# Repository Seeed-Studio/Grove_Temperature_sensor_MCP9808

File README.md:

Grove Temperature sensor MCP9808  
==============

Introduction of sensor
----------------------------  
Microchip Technology Inc.’s MCP9808 digital temperature sensor converts temperatures between -20°C and +100°C to a digital word with
±0.25°C/±0.5°C (typical/maximum) accuracy.  

***
Usage:
==========
Download all the source files.
There are two examples for user to use.
>* **example/MCP9808_basic_demo/MCP9808_basic_demo.ino**:This example is a sample use of temperature sensor,you need to polling for data. 
>* **example/MCP9808_demo_with_limit/MCP9808_demo_with_limit.ino**,There is a alert pad on the sensor module which connect to alert pin.You can set temperature limits by calling the API we provided.The alert pin outputs low when the temperature value beyond limit.Otherwise stays high.You can attach alert pin to a interrupt pin of host,To improve the efficiency of program operation.

Reference:
===============
Refer to the **/doc** to get more detail.

***
This software is written by downey  for seeed studio<br>
Email:dao.huang@seeed.cc
and is licensed under [The MIT License](http://opensource.org/licenses/mit-license.php). Check License.txt for more information.<br>

Contributing to this software is warmly welcomed. You can do this basically by<br>
[forking](https://help.github.com/articles/fork-a-repo), committing modifications and then [pulling requests](https://help.github.com/articles/using-pull-requests) (follow the links above<br>
for operating guide). Adding change log and your contact into file header is encouraged.<br>
Thanks for your contribution.

Seeed Studio is an open hardware facilitation company based in Shenzhen, China. <br>
Benefiting from local manufacture power and convenient global logistic system, <br>
we integrate resources to serve new era of innovation. Seeed also works with <br>
global distributors and partners to push open hardware movement.<br>

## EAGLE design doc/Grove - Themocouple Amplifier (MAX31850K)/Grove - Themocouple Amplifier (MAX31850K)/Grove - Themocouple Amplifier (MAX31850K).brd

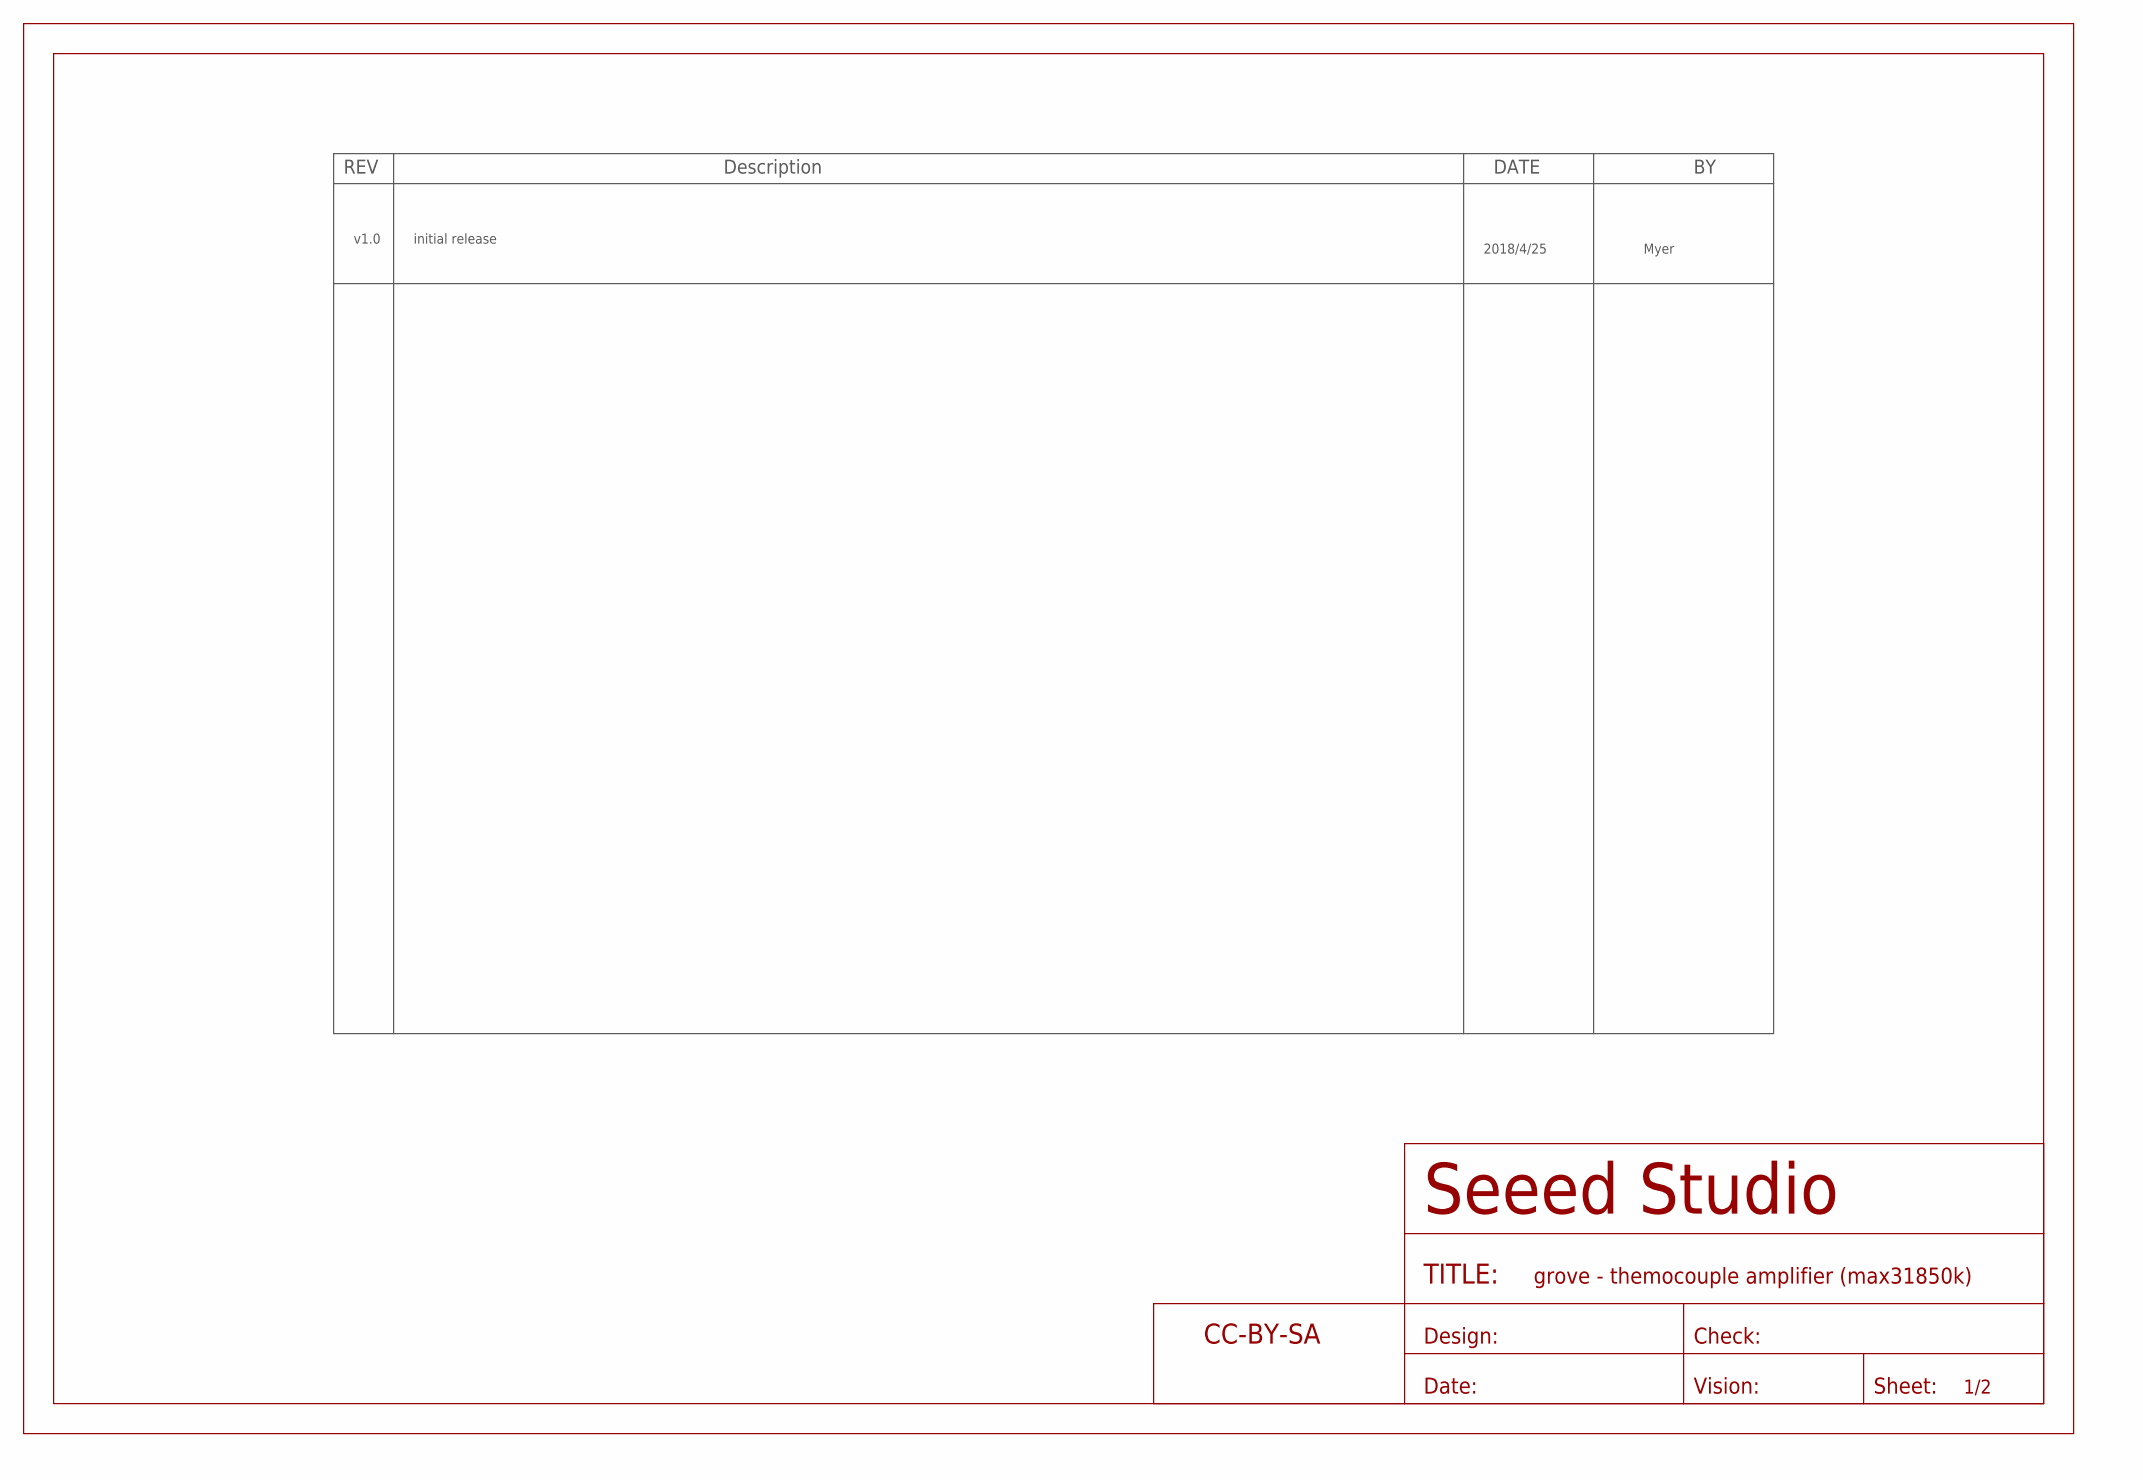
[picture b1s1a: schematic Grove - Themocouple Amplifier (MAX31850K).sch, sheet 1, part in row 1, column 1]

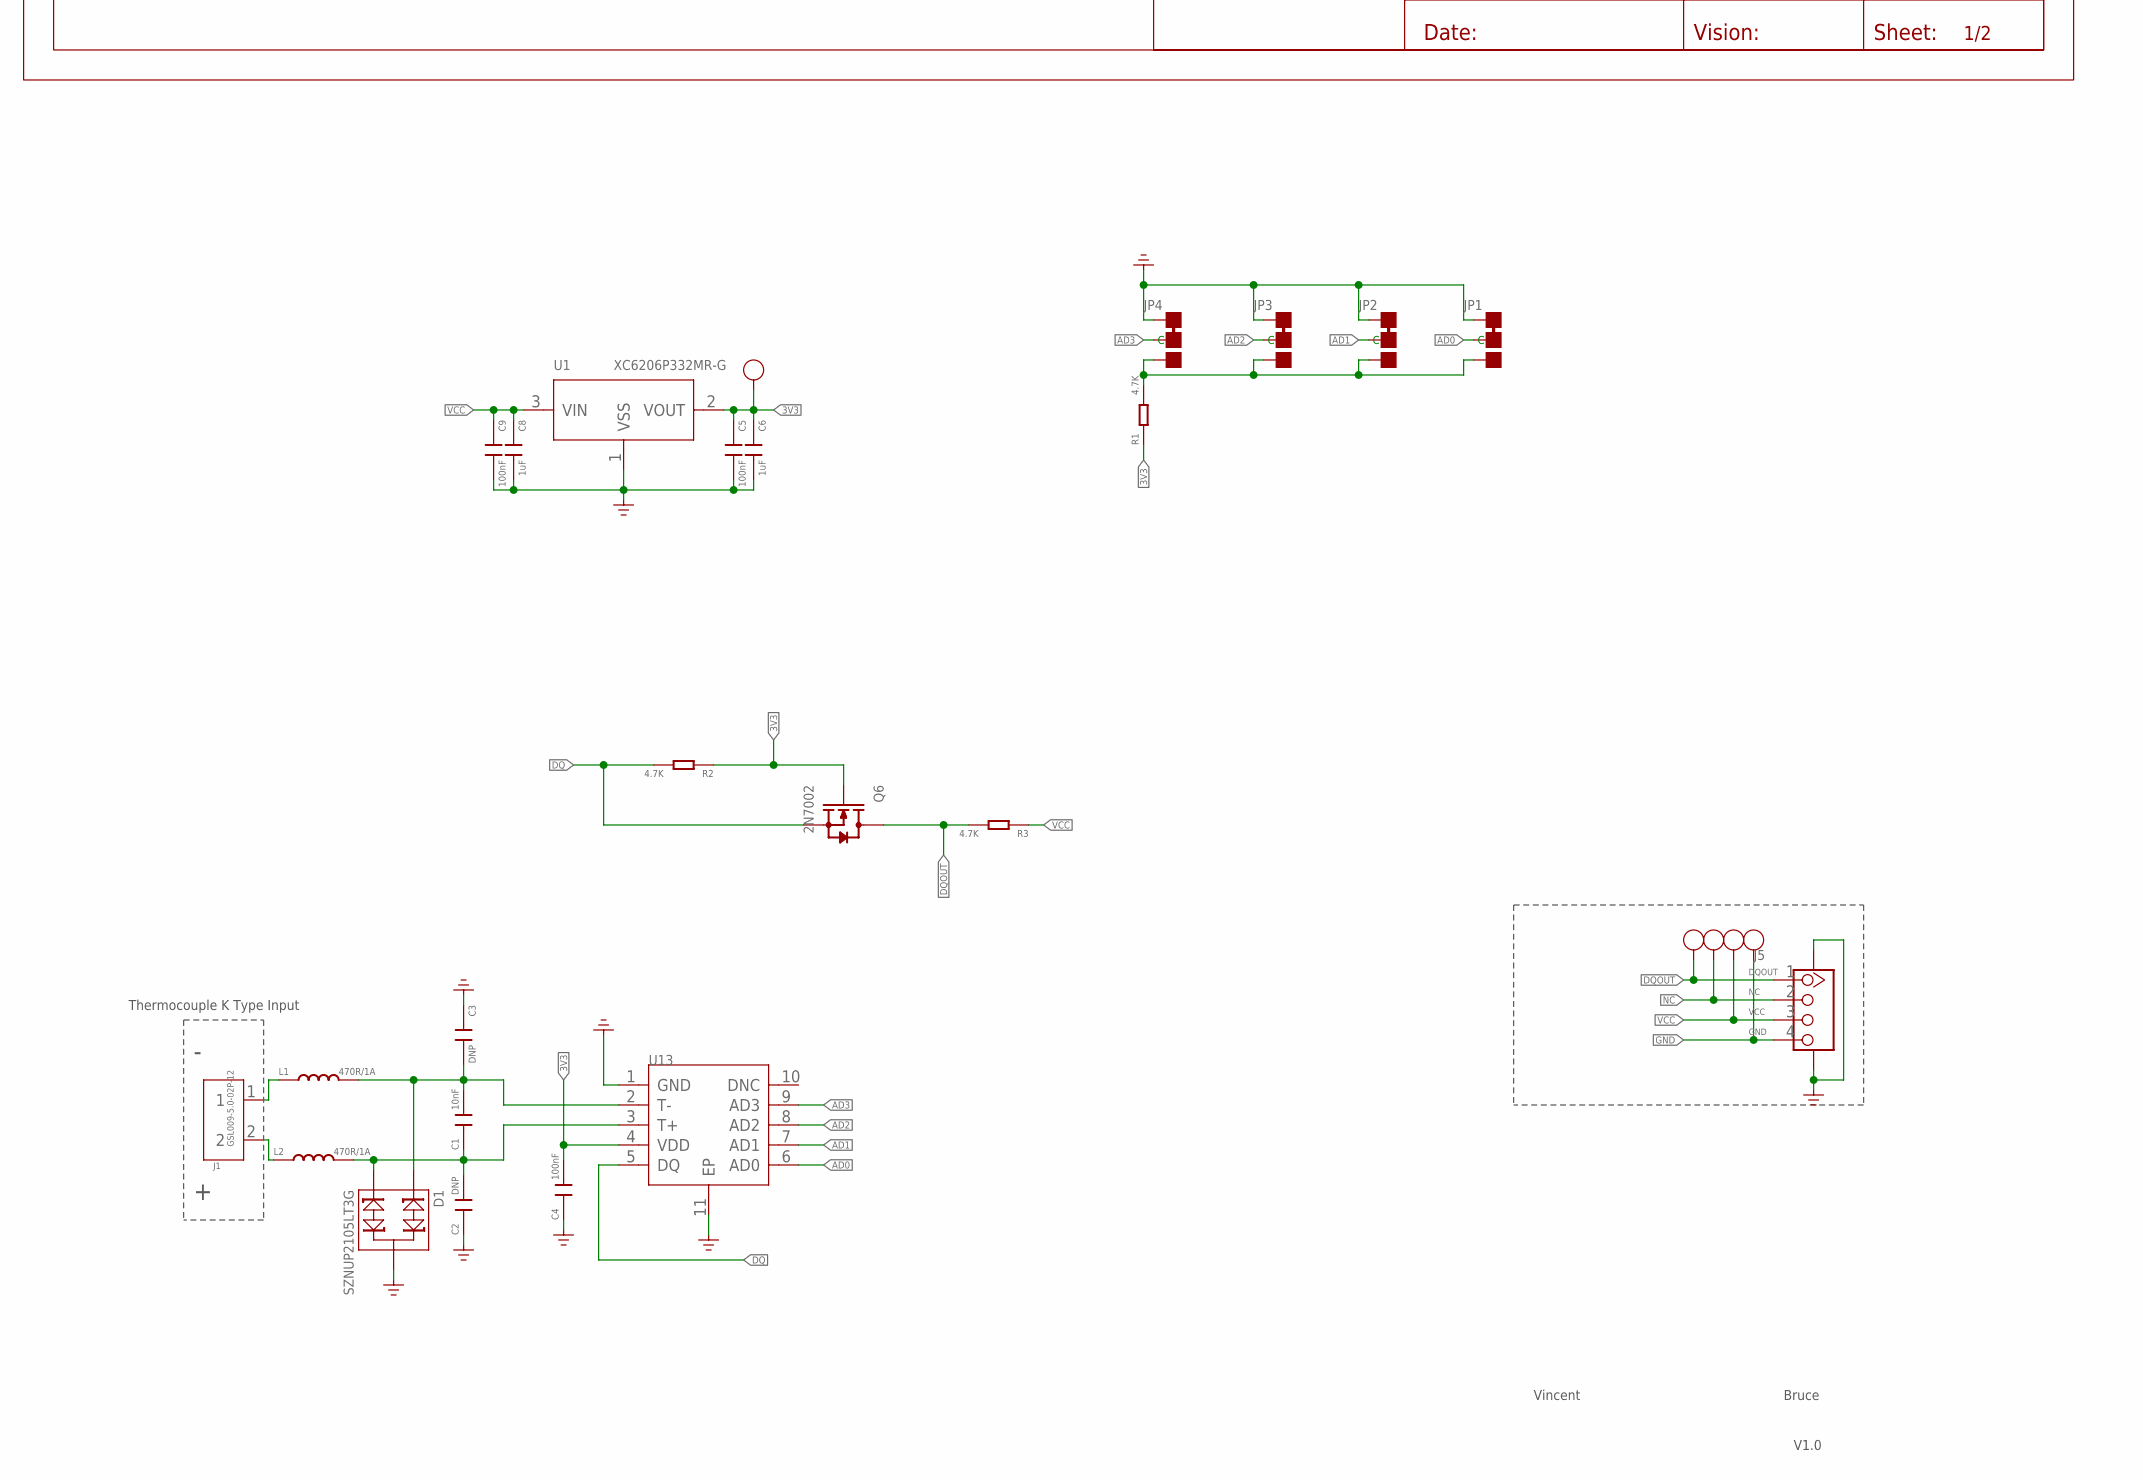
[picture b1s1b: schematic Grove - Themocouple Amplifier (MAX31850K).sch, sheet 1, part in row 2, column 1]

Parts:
C1: 10nF; C0805
C2, C3: DNP; C0603
C4, C5, C9: 100nF; C0603
C6, C8: 1uF; C0603
D1: SZNUP2105LT3G; SOT-23
FR2: SEEEDSTUDIO-OPEN-SCH-FRAME; SEEEDSTUDIO-PCB-FRAME
GND4: TEST-POINT'4545'; TP-D45MIL
J1: GSL009-5.0-02P-12; 2P-5.0-10.6X10X14.8H
J5: GROVE-CONNECTOR-SMD'90D'; HW4-SMD-2.0-90D
JP1, JP2, JP3, JP4: JP-3P-SHORT; 3P-SMD-SHORT
L1, L2: 470R/1A; L0603
Q6: 2N7002; SOT-323
R1, R2, R3: 4.7K; R0603
SCL: TEST-POINT'4545'; TP-D45MIL
SDA3, SDA4: TEST-POINT'4545'; TP-D45MIL
U1: XC6206P332MR-G; SOT-23
U13: CONVERTER-MAX31850; TDFN10-0.5-3X4MM
VCC1: TEST-POINT'4545'; TP-D45MIL

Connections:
3V3: C4.2, C5.1, C6.1, Q6.1 (G), R1.1, R2.1, SDA3.T, U1.2 (VOUT), U13.4 (VDD)
AD0: JP1.MM (C), U13.6 (AD0)
AD1: JP2.MM (C), U13.7 (AD1)
AD2: JP3.MM (C), U13.8 (AD2)
AD3: JP4.MM (C), U13.9 (AD3)
DQ: Q6.2 (S), R2.2, U13.5 (DQ)
DQOUT: GND4.T, J5.1, Q6.3 (D), R3.2
GND: C2.1, C3.1, C4.1, C5.2, C6.2, C8.2, C9.2, D1.3, J5.4, J5.SS1, J5.SS2, JP1.11 (L), JP2.11 (L), JP3.11 (L), JP4.11 (L), SCL.T, U1.1 (VSS), U13.1 (GND), U13.11 (EP)
unnamed: J1.1, L1.1
unnamed: J1.2, L2.1
unnamed: JP1.00 (R), JP2.00 (R), JP3.00 (R), JP4.00 (R), R1.2
unnamed: C1.2, C3.2, D1.1, L1.2, U13.2 (T-)
unnamed: C1.1, C2.2, D1.2, L2.2, U13.3 (T+)
NC: J5.2, VCC1.T
VCC: C8.1, C9.1, J5.3, R3.1, SDA4.T, U1.3 (VIN)

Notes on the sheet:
Vincent
V1.0
Bruce
Thermocouple K Type Input
v1.0
initial release
2018/4/25
Myer

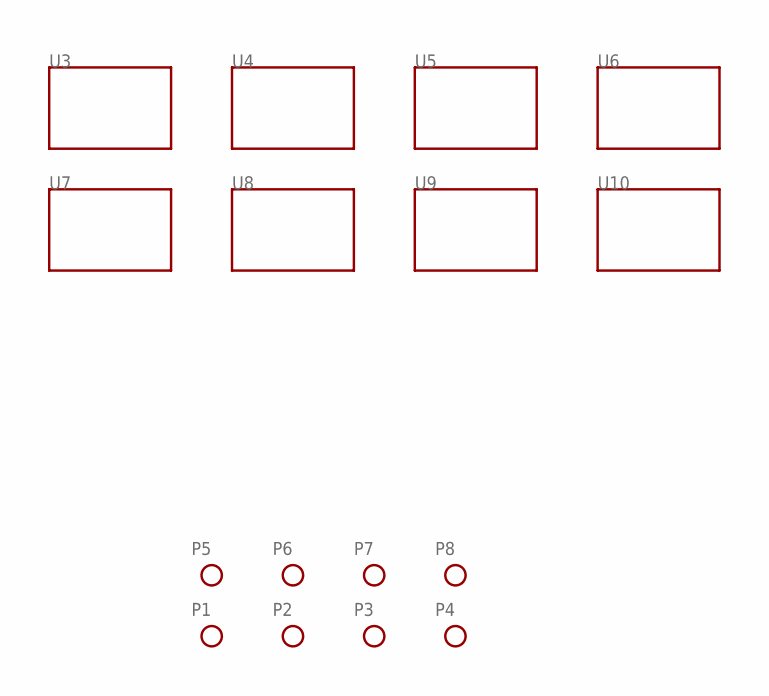
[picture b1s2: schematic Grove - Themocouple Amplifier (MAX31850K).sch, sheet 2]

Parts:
P1, P2, P3, P4, P5, P6, P7, P8: PAD-MARK; ROUND-MARK-1.0
U3, U4, U5, U6, U7, U8, U9, U10: TWIG'2U'; GROVE-TEST-PLATFORM

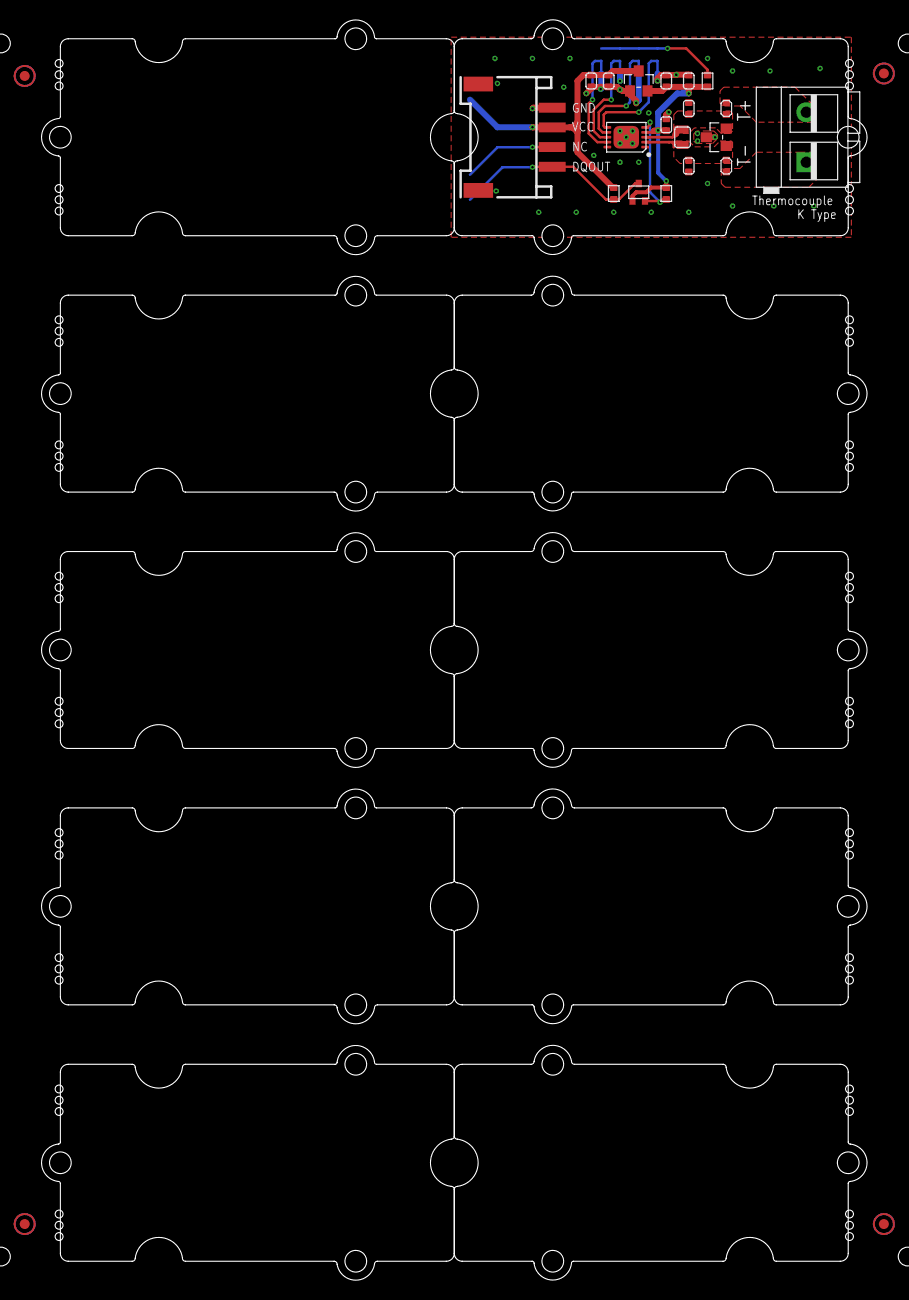
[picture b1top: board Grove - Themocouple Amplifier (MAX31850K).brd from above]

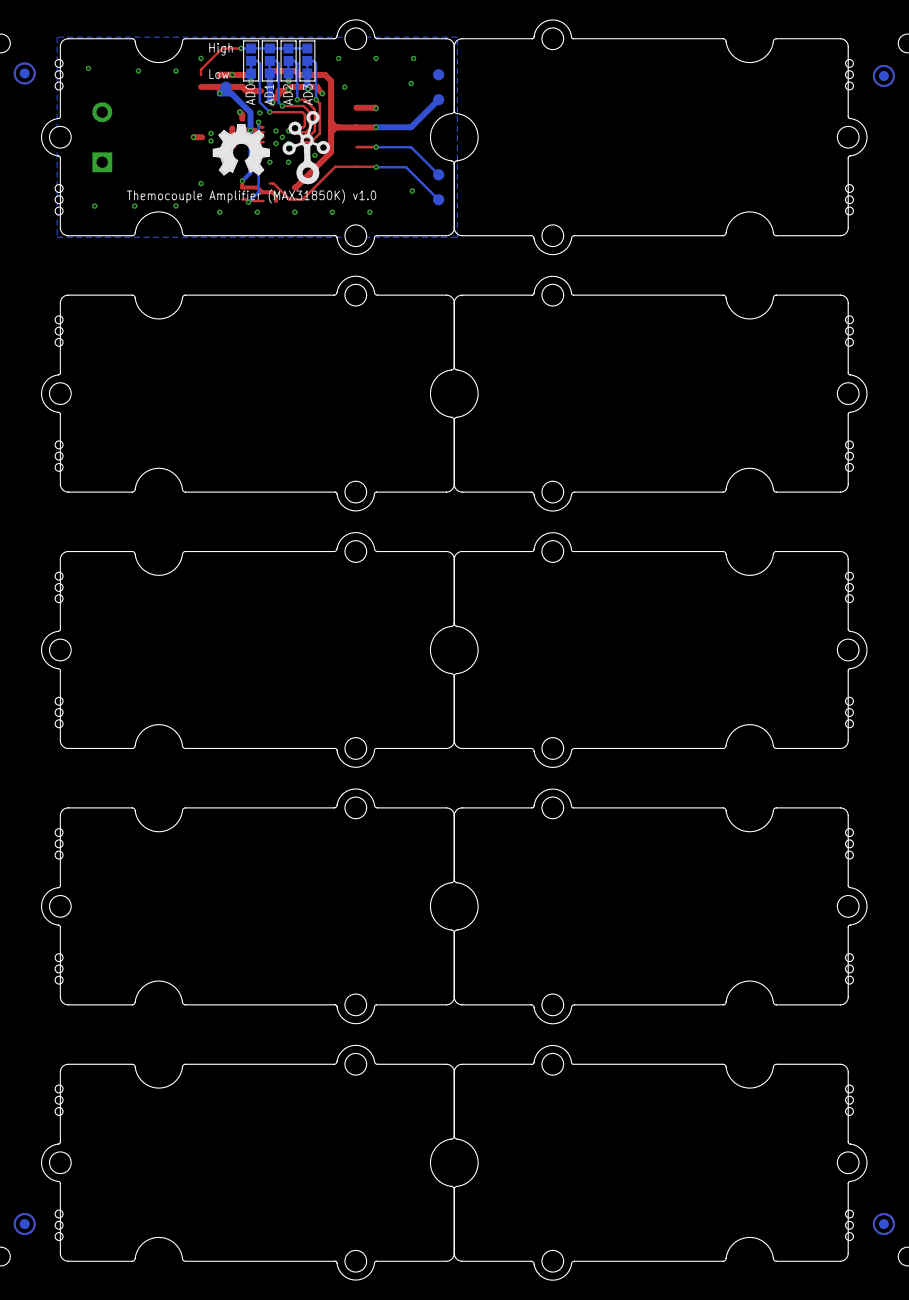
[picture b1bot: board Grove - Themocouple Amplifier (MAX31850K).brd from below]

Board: 2 copper layers, 83.8 x 128.0 mm, 49 parts (15 on the bottom side), 15 nets.

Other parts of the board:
U11, U12: GROVE-TEST-PLATFORM@1
U$2: GROVE-SILK-BIG
U$5: OSHW_FILLX200_NOTEXT

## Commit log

2018-05-18 arduino example
2018-05-18 source file
2018-05-21 keyword.txt
2018-05-21 license
2018-05-21 arduino examples
2018-05-21 picture
2018-10-19 fix: compatible
2018-10-19 fix :fix naming conflict
2020-02-03 Pretty printed the Arduino code with astyle
2020-02-04 Seeed:Arduino: Add travis.yml
2020-02-04 Seeed:Arduino: Add travis build status
2020-05-12 Seeed:Arduino: fix travis.yml write error
2020-05-18 Fix typo in example code comment
2024-02-14 Namespaced variable to avoid conflict with LwIP library as used in Espressif ESP-IDF.
2024-02-18 Namespaced variable to avoid conflict with LwIP library as used in Espressif ESP-IDF. (#3)
2024-02-18 Update MCP9808_basic_demo.ino (#2)
2024-10-08 Add sync_issues GitHub Action for workflows
2024-12-23 ci: add an action to run ci-arduino
2025-01-08 ci: add an action to automatically close stale issues and PRs

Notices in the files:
parts and their libraries:
moudle-new: This work is licensed under the Creative Commons Attribution 4.0 International License.
To view a copy of this license,visit:
http://creativecommons.org/licenses/by-sa/4.0
moudle-new: CC-BY-SA
